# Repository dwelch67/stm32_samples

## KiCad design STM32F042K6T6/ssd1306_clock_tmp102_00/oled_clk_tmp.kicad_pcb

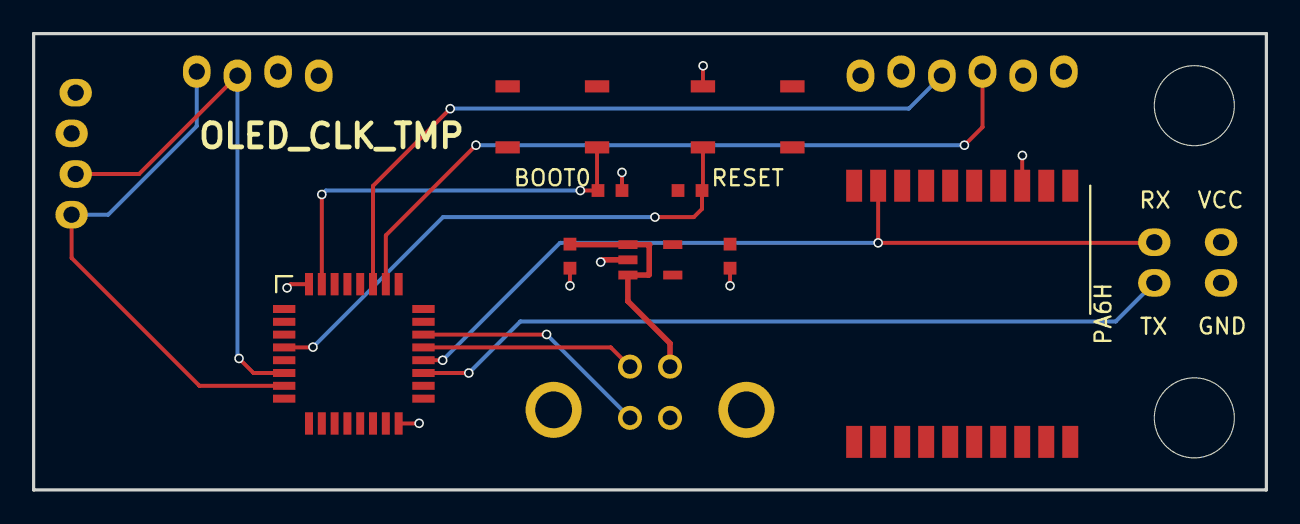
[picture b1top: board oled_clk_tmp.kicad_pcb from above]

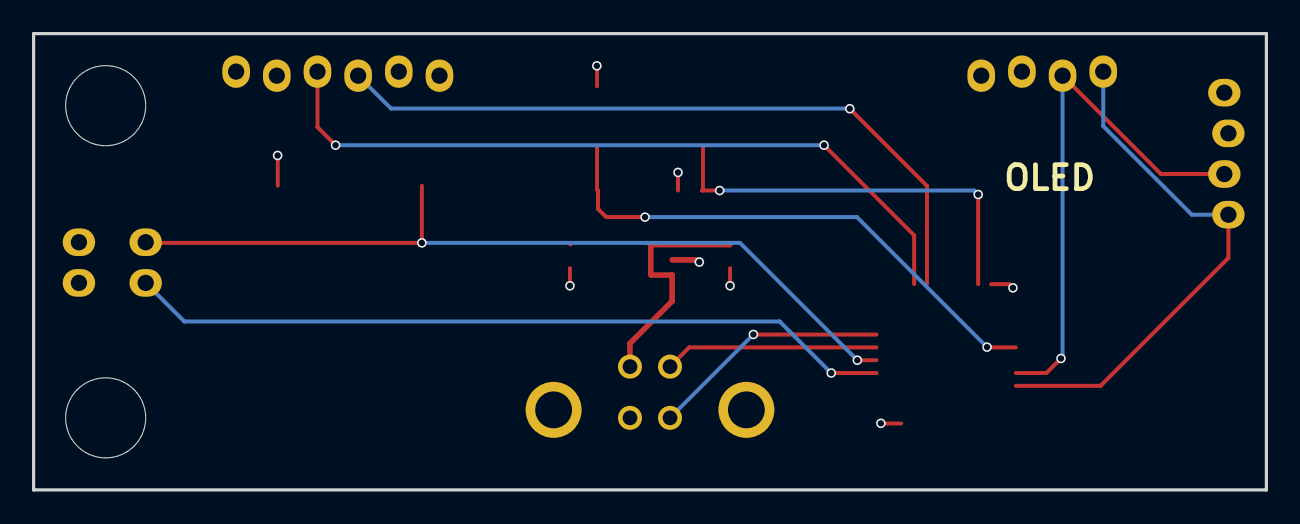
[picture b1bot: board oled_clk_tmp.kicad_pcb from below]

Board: 2 copper layers, 77.0 x 28.5 mm, 11 parts (3 on the bottom side), 7 nets.

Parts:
AP2112: AP2112
BOOT0: BUTTON4_SMD
C: C_0603
C#2: C_0603
OLED128x32: OLED128x32
OLED128x64: OLED128x64
PA6H: GPS; PA6H
R: R_0603
R#2: R_0603
RESET: BUTTON4_SMD
TMP102: TMP102

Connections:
/boot0: BOOT0.2, R.BOOT
/gnd: AP2112.GND, C.GND, C#2.GND, OLED128x32.GND, OLED128x64.GND, PA6H.GND, R.GND, RESET.3, TMP102.GND
/nrst: R#2.NRST, RESET.1
/scl0: OLED128x32.SCL, OLED128x64.SCL
/sda0: OLED128x32.SDA, OLED128x64.SDA
/vcc: AP2112.VOUT, BOOT0.4, C#2.VCC, OLED128x32.VCC, OLED128x64.VCC, PA6H.VCC, R#2.VCC, TMP102.VCC
/vin: AP2112.EN, AP2112.VIN, C.VIN

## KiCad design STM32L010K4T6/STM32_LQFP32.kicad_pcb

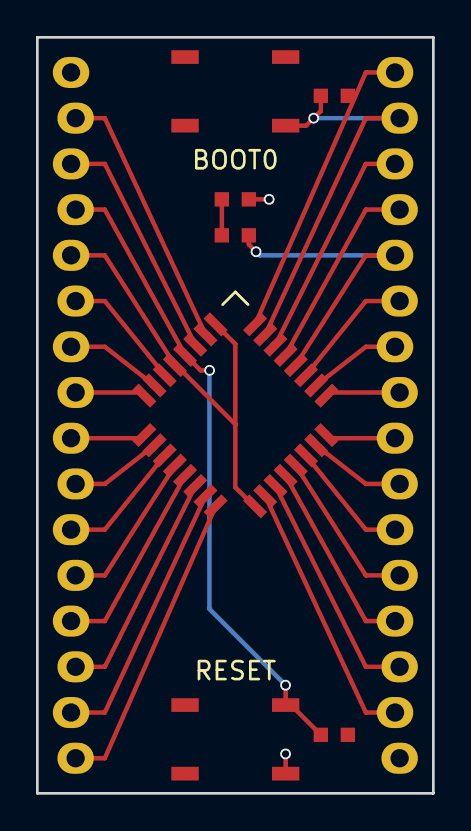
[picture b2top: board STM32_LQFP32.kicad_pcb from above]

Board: 2 copper layers, 22.0 x 42.0 mm, 7 parts (0 on the bottom side), 2 nets.

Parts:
BOOT0: BUTTON4_SMD
L: L_0603
LQFP32: STM32_LQFP32
R: R_0603
R#2, R#3: R_0603
RESET: BUTTON4_SMD

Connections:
/gnd: L.2, LQFP32.GND, RESET.2
/vcc: BOOT0.1, LQFP32.3.3, R#2.2
